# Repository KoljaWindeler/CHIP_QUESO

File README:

please read http://koljawindeler.github.io/CHIP_QUESO

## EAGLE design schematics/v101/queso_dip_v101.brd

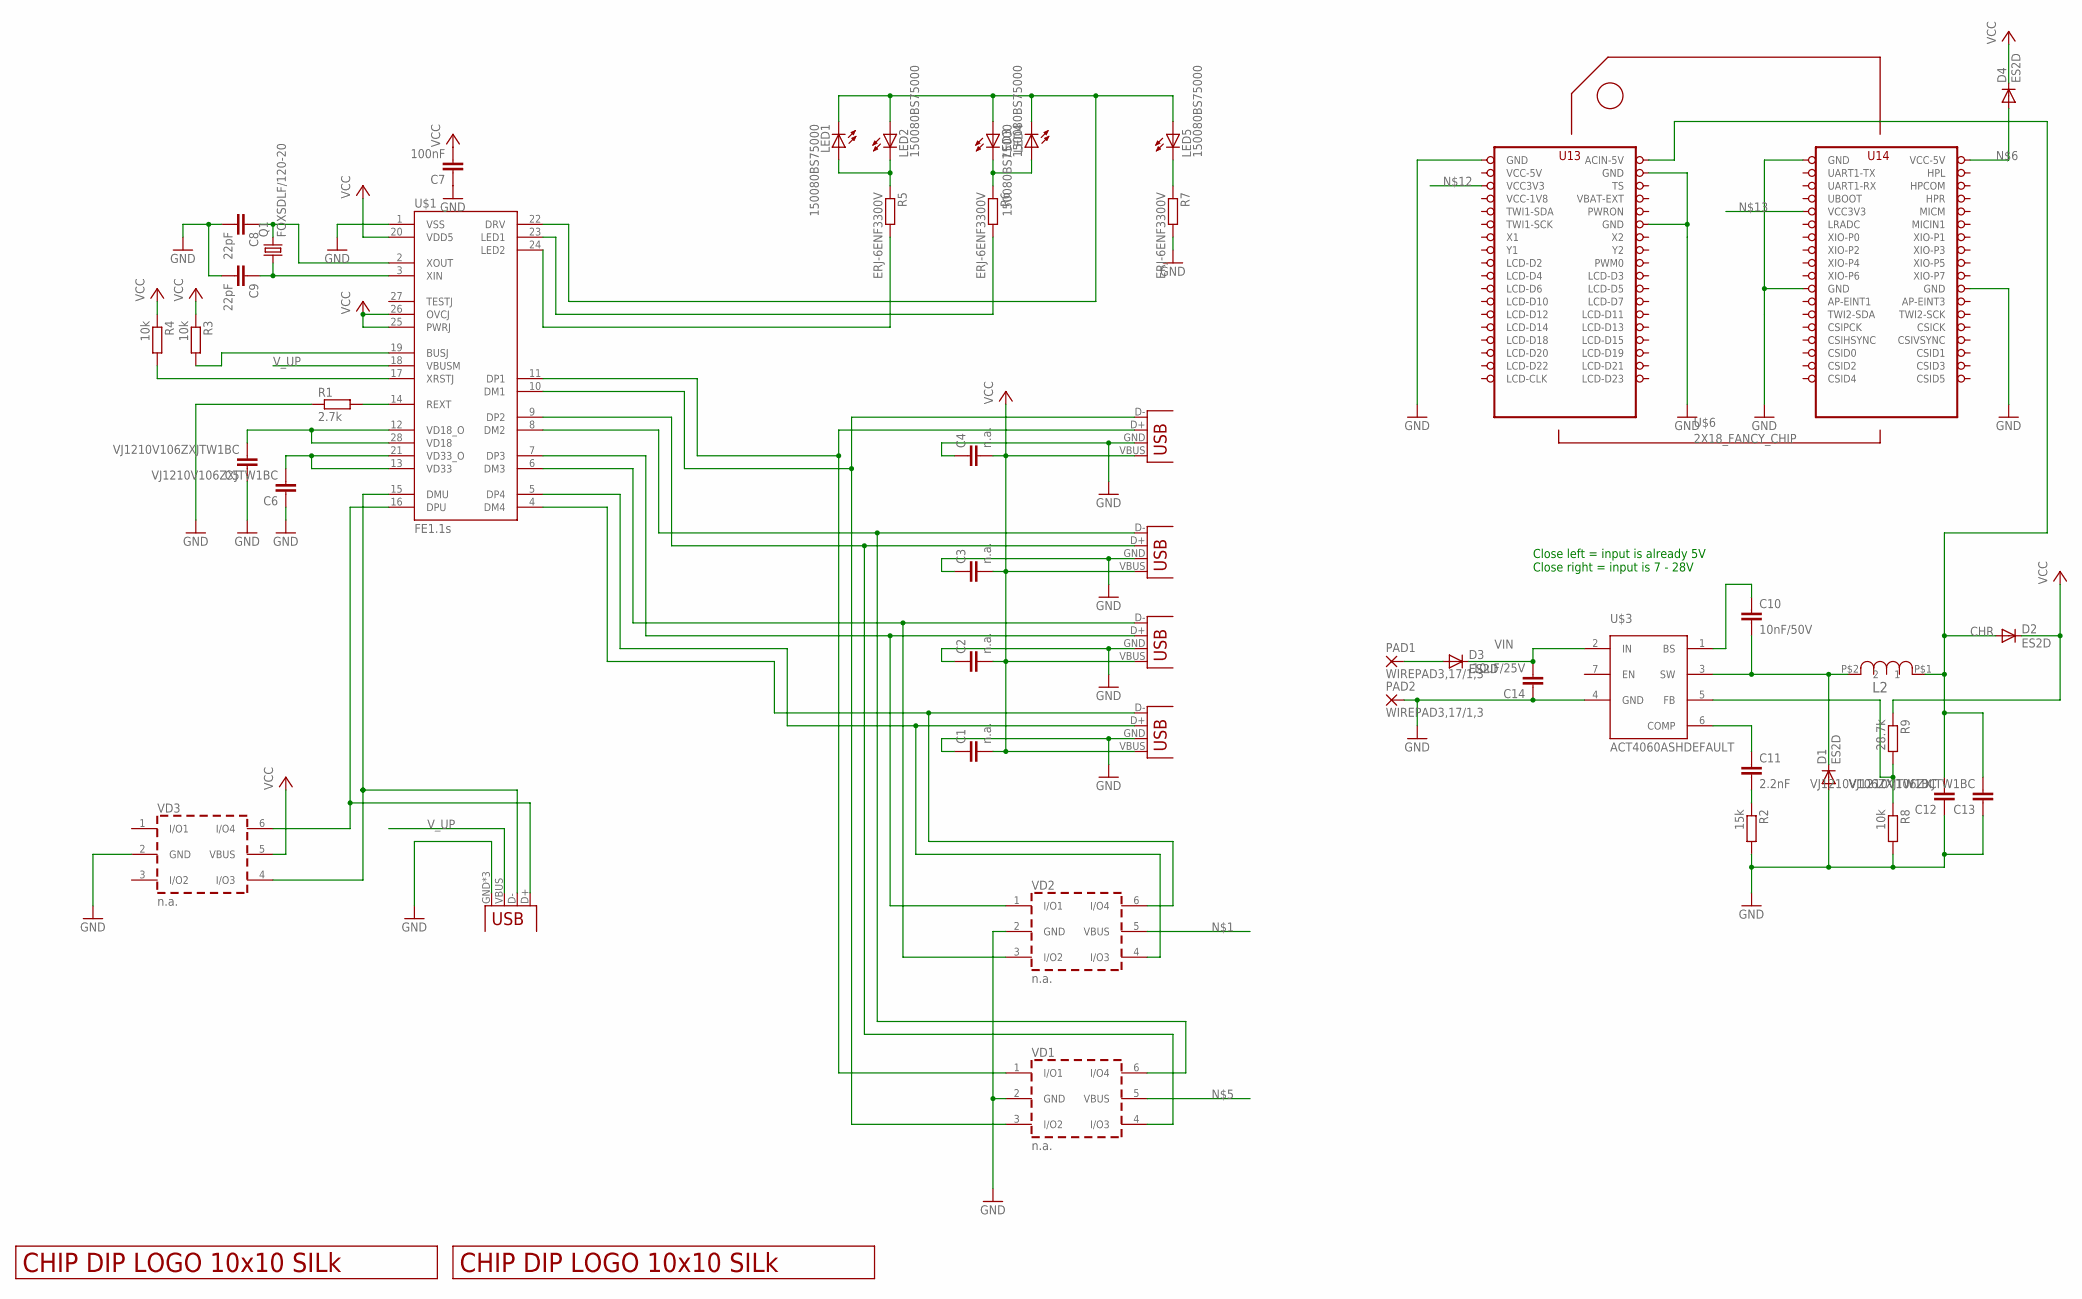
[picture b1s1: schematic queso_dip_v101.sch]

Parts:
C1, C2, C3, C4: n.a.; C1210
C5, C6, C12, C13: VJ1210V106ZXJTW1BC; C1210
C7: 100nF; C0805
C8, C9: 22pF; C0805
C10: 10nF/50V; C0805
C11: 2.2nF; C0805
C14: 10uF/25V; C1210
D1, D2, D3, D4: ES2D; SMB
DATA_USB: USBUSB-MICROB-SMT-DIP; USB-MICROB-SMT-DIP
L2: SRN6045-100M; SRN6045
LED1, LED2, LED3, LED4, LED5: 150080BS75000; CHIP-LED0805
PAD1, PAD2: WIREPAD3,17/1,3; 3,17/1,3
Q1: FOXSDLF/120-20; SM49
R1: 2.7k; R0805
R2: 15k; R0805
R3, R4, R8: 10k; R0805
R5, R6, R7: ERJ-6ENF3300V; R0805
R9: 28.7k; R0805
U$1: FE1.1S; FE1.1S_SSOP-28
U$2, U$4: LOGO_10X10_SILK; LOGO2_10X10_SILK
U$3: ACT4060ASHDEFAULT; SOP-8
U$6: 2X18_FANCY_CHIP; 2X18_FANCY_EDGE_CHIP_TH
VD1, VD2, VD3: n.a.; SOT-23-6L
X1, X2, X3, X4: USB-A-HU

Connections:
CHR: C12.2, C13.2, D2.A, L2.P$1 (1), U$6.36 (ACIN-5V)
DM1: U$1.10 (DM1), VD1.3 (I/O2), X4.D- (D+)
DM2: U$1.8 (DM2), VD1.6 (I/O4), X3.D- (D+)
DM3: U$1.6 (DM3), VD2.3 (I/O2), X2.D- (D+)
DM4: U$1.4 (DM4), VD2.6 (I/O4), X1.D- (D+)
DMU: DATA_USB.D-, U$1.15 (DMU), VD3.4 (I/O3)
DP1: U$1.11 (DP1), VD1.1 (I/O1), X4.D+ (D-)
DP2: U$1.9 (DP2), VD1.4 (I/O3), X3.D+ (D-)
DP3: U$1.7 (DP3), VD2.1 (I/O1), X2.D+ (D-)
DP4: U$1.5 (DP4), VD2.4 (I/O3), X1.D+ (D-)
DPU: DATA_USB.D+, U$1.16 (DPU), VD3.6 (I/O4)
GND: C1.1, C2.1, C3.1, C4.1, C5.1, C6.1, C7.1, C8.2, C9.2, C12.1, C13.1, C14.1, D1.A, DATA_USB.GND, DATA_USB.MT1 (GND), DATA_USB.MT2 (GND), PAD2.1, R1.1, R7.2, R8.2, U$1.1 (VSS), U$3.4 (GND), U$6.26 (GND), U$6.34 (GND), U$6.35 (GND), U$6.51 (GND), U$6.52 (GND), U$6.71 (GND), VD1.2 (GND), VD2.2 (GND), VD3.2 (GND), X1.GND (VBUS), X2.GND (VBUS), X3.GND (VBUS), X4.GND (VBUS)
unnamed: D3.A, PAD1.1
unnamed: D4.A, U$6.72 (VCC-5V)
unnamed: C10.2, D1.C, L2.P$2 (2), U$3.3 (SW)
unnamed: C10.1, U$3.1 (BS)
unnamed: C11.2, R2.1
unnamed: C11.1, U$3.6 (COMP)
unnamed: R8.1, R9.2, U$3.5 (FB)
unnamed: R5.2, U$1.24 (LED2)
unnamed: R6.2, U$1.23 (LED1)
unnamed: C6.2, U$1.13 (VD33), U$1.21 (VD33_O)
unnamed: C5.2, U$1.12 (VD18_O), U$1.28 (VD18)
unnamed: R1.2, U$1.14 (REXT)
unnamed: R4.2, U$1.17 (XRSTJ)
unnamed: R3.2, U$1.19 (BUSJ)
unnamed: C8.1, Q1.2, U$1.2 (XOUT)
unnamed: C9.1, Q1.1, U$1.3 (XIN)
unnamed: LED5.C, R7.1
unnamed: LED3.C, LED4.A, R6.1
unnamed: LED1.A, LED2.C, R5.1
unnamed: LED1.C, LED2.A, LED3.A, LED4.C, LED5.A, U$1.22 (DRV)
VCC: C1.2, C2.2, C3.2, C4.2, C7.2, D2.C, D4.C, R3.1, R4.1, R9.1, U$1.20 (VDD5), U$1.25 (PWRJ), U$1.26 (OVCJ), VD3.5 (VBUS), X1.VBUS (GND), X2.VBUS (GND), X3.VBUS (GND), X4.VBUS (GND)
VCC-1V8: U$6.29 (VCC-1V8)
VCC-5V: U$6.33 (VCC-5V)
VIN: C14.2, D3.C, U$3.2 (IN)
V_UP: DATA_USB.VBUS, U$1.18 (VBUSM)

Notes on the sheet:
Close left = input is already 5V Close right = input is 7 - 28V

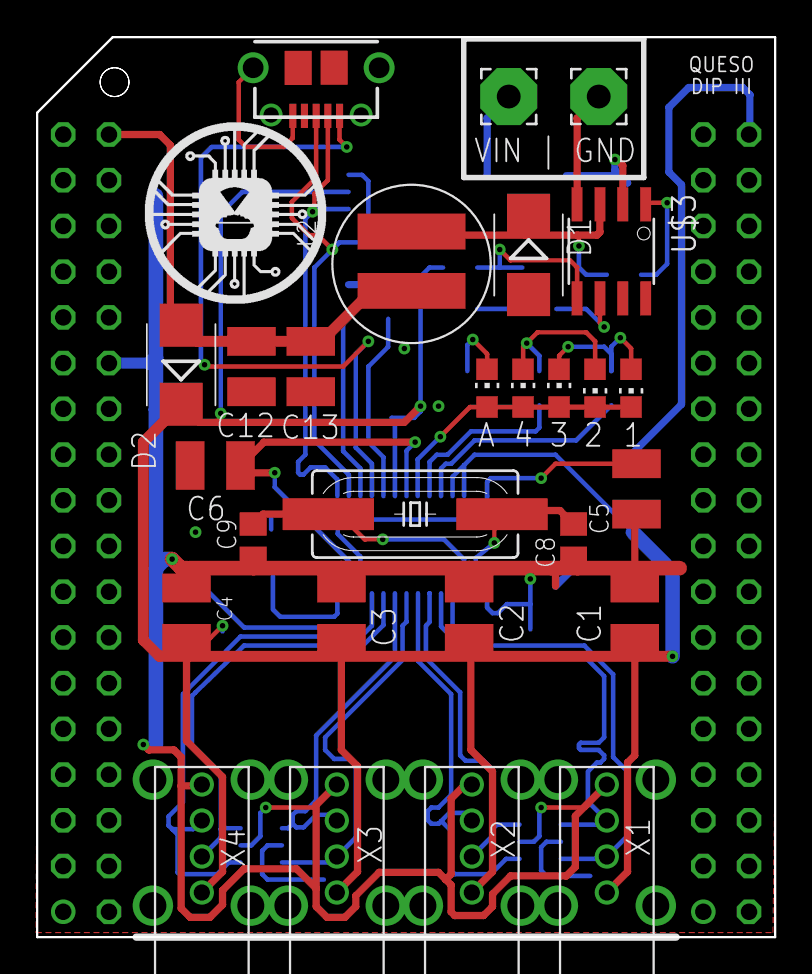
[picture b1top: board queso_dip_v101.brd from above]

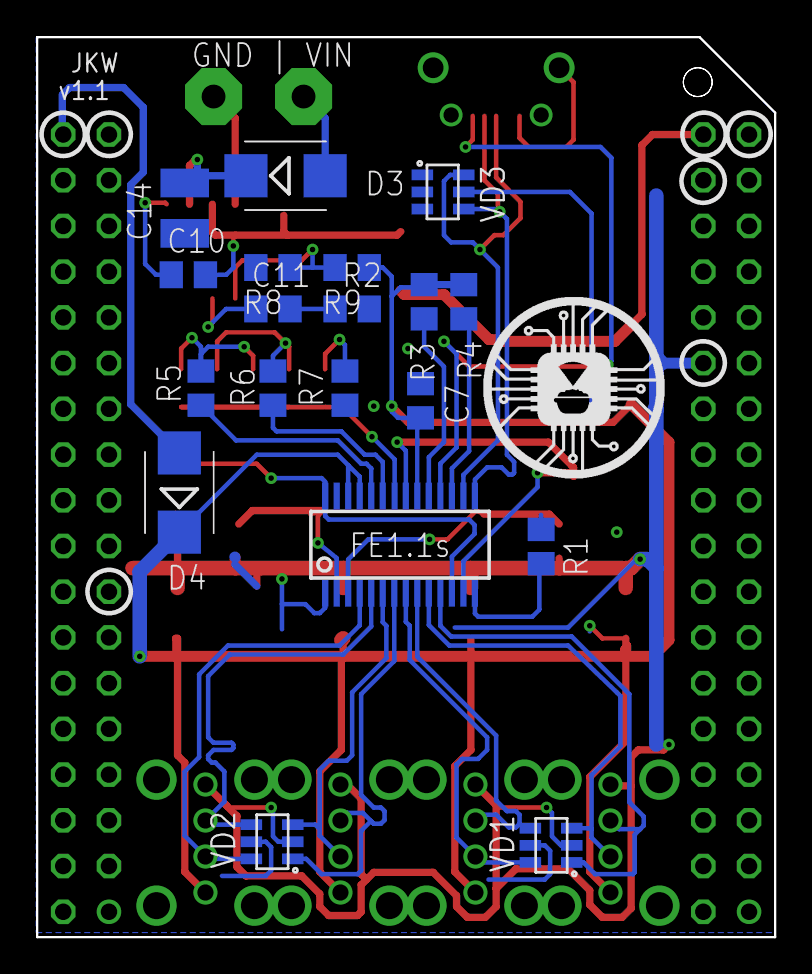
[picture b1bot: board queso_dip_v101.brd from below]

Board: 2 copper layers, 41.0 x 50.0 mm, 49 parts (20 on the bottom side), 35 nets.

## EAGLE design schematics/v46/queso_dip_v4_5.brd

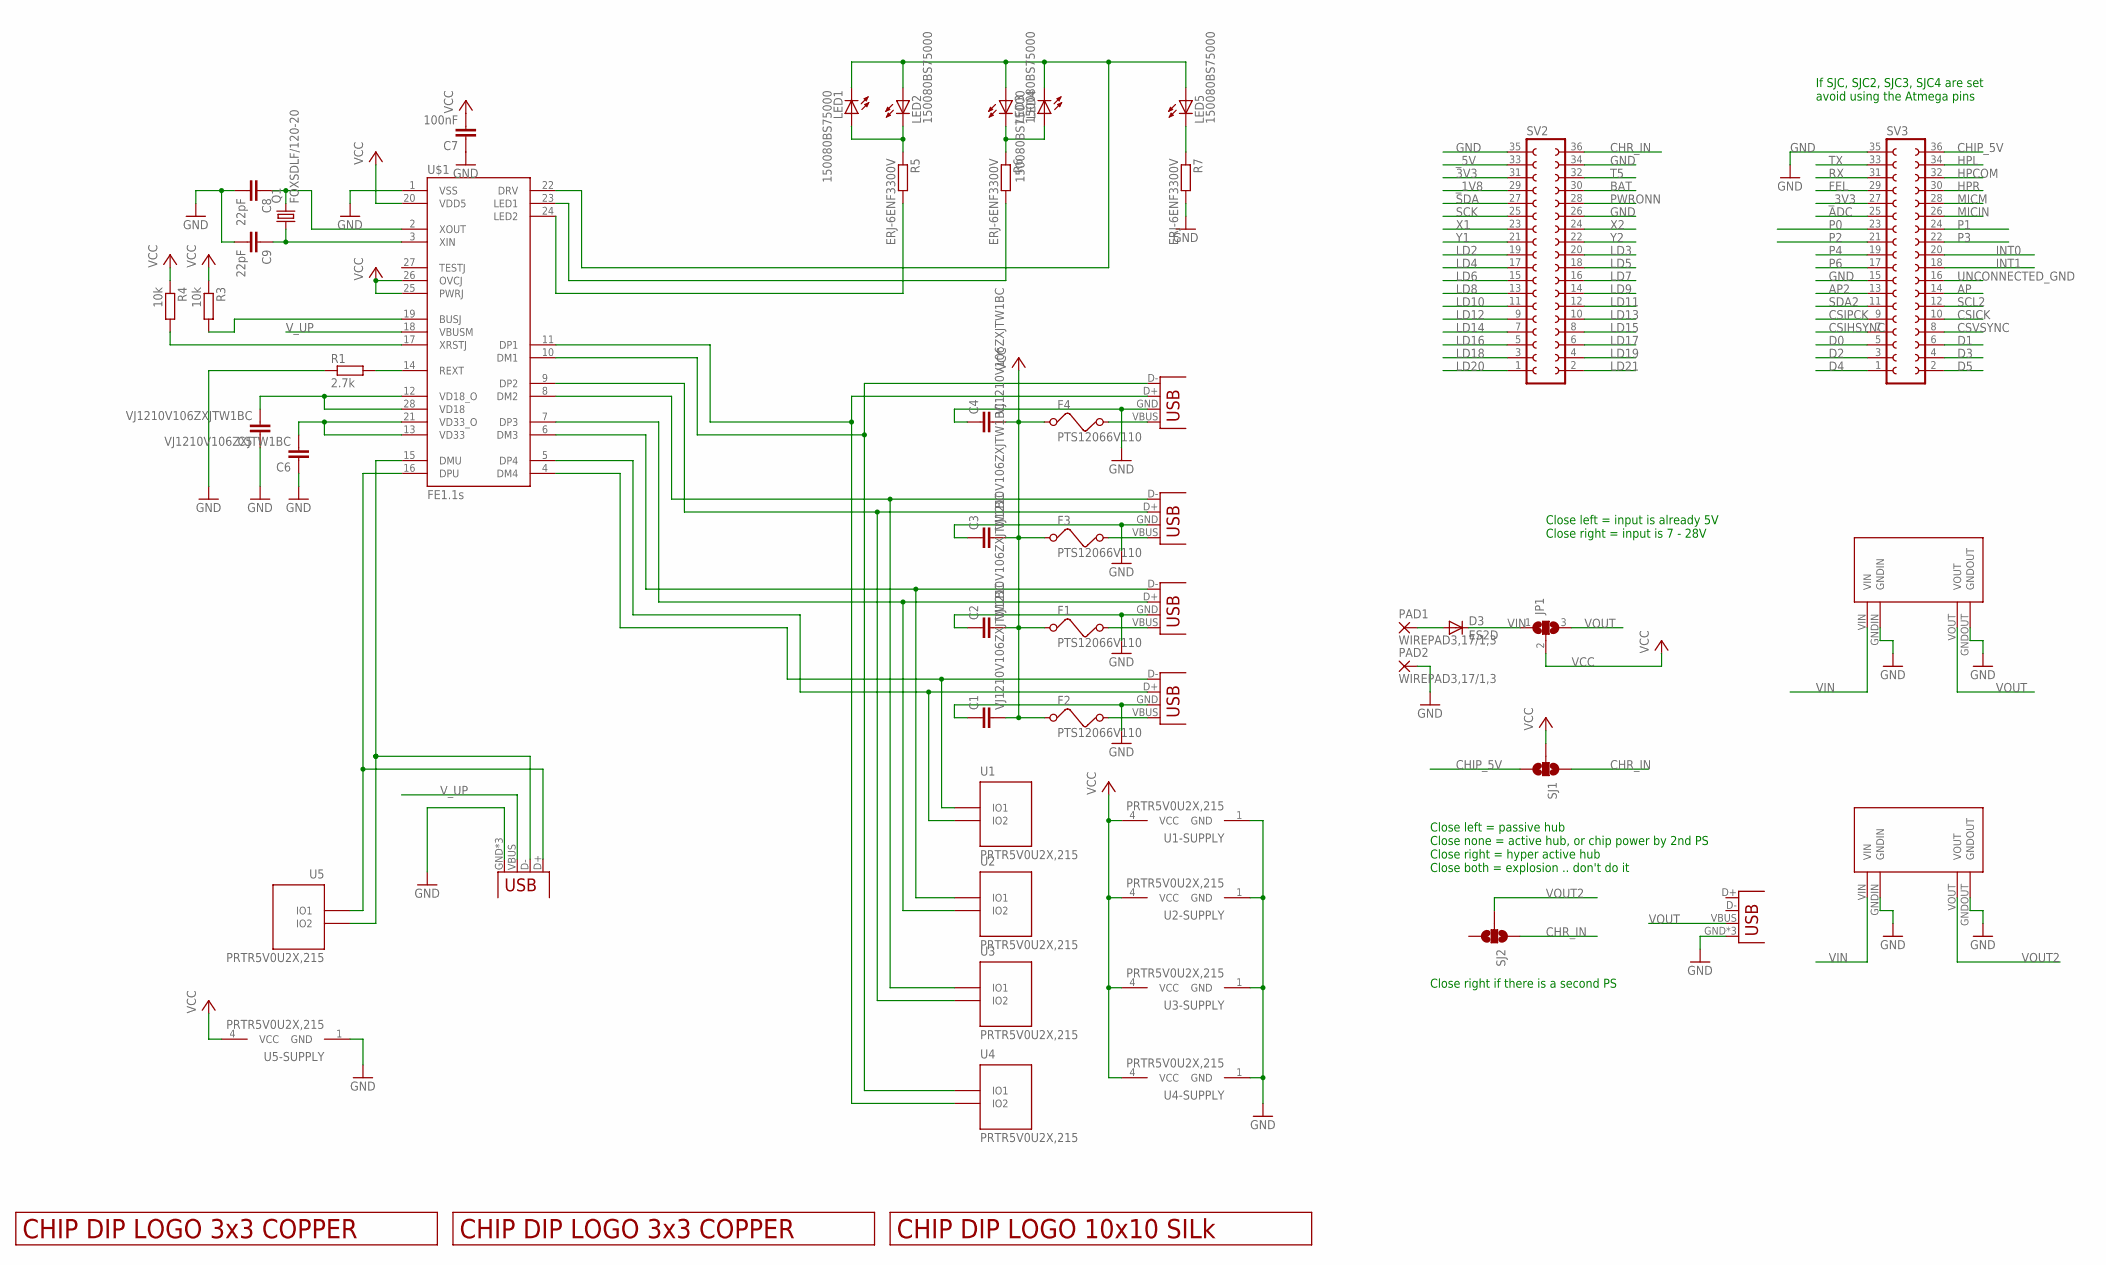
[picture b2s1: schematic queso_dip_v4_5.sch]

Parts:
C1, C2, C3, C4, C5, C6: VJ1210V106ZXJTW1BC; C1210
C7: 100nF; C0805
C8, C9: 22pF; C0805
D3: ES2D; SMB
F1, F2, F3, F4: PTS12066V110; 1210
JP1: SJ2W; SJ_2
LED1, LED2, LED3, LED4, LED5: 150080BS75000; CHIP-LED0805
PAD1, PAD2: WIREPAD3,17/1,3; 3,17/1,3
Q1: FOXSDLF/120-20; SM49
R1: 2.7k; R0805
R3, R4: 10k; R0805
R5, R6, R7: ERJ-6ENF3300V; R0805
SJ1, SJ2: SOLDERJUMPER_2WAYT; SJ_2
SV2, SV3: FE18-2
U1, U2, U3, U4, U5: PRTR5V0U2X,215; SOT-143B
U$1: FE1.1S; FE1.1S_SSOP-28
U$2, U$4: LOGO_3X3_COPPER
U$3, U$9: MP1584EN
U$5: LOGO_10X10_SILK
USB, USB1: USBUSB-MICROB-SMT-DIP; USB-MICROB-SMT-DIP
X1, X2, X3, X4: USB-A-HU

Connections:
3V3: SV2.31
ADC: SV3.25
AP: SV3.14
AP2: SV3.13
BAT: SV2.30
CHIP_5V: SJ1.3, SV3.36
CHR_IN: SJ1.1, SJ2.1, SV2.36
CSICK: SV3.10
CSIHSYNC: SV3.7
CSIPCK: SV3.9
CSVSYNC: SV3.8
D0: SV3.5
D1: SV3.6
D2: SV3.3
D3: SV3.4
D4: SV3.1
D5: SV3.2
DM1: U4.2 (IO1), U$1.10 (DM1), X4.D- (D+)
DM2: U3.2 (IO1), U$1.8 (DM2), X3.D- (D+)
DM3: U2.2 (IO1), U$1.6 (DM3), X2.D- (D+)
DM4: U1.2 (IO1), U$1.4 (DM4), X1.D- (D+)
DMU: U5.3 (IO2), U$1.15 (DMU), USB.D-
DP1: U4.3 (IO2), U$1.11 (DP1), X4.D+ (D-)
DP2: U3.3 (IO2), U$1.9 (DP2), X3.D+ (D-)
DP3: U2.3 (IO2), U$1.7 (DP3), X2.D+ (D-)
DP4: U1.3 (IO2), U$1.5 (DP4), X1.D+ (D-)
DPU: U5.2 (IO1), U$1.16 (DPU), USB.D+
FEL: SV3.29
GND: C1.1, C2.1, C3.1, C4.1, C5.1, C6.1, C7.1, C8.2, C9.2, PAD2.1, R1.1, R7.2, SV2.26, SV2.34, SV2.35, SV3.15, SV3.35, U1.1 (GND), U2.1 (GND), U3.1 (GND), U4.1 (GND), U5.1 (GND), U$1.1 (VSS), U$3.GNDIN, U$3.GNDOUT, U$9.GNDIN, U$9.GNDOUT, USB.GND, USB.MT1 (GND), USB.MT2 (GND), USB1.GND, USB1.MT1 (GND), USB1.MT2 (GND), X1.GND (VBUS), X2.GND (VBUS), X3.GND (VBUS), X4.GND (VBUS)
HPCOM: SV3.32
HPL: SV3.34
HPR: SV3.30
INT0: SV3.20
INT1: SV3.18
LD2: SV2.19
LD3: SV2.20
LD4: SV2.17
LD5: SV2.18
LD6: SV2.15
LD7: SV2.16
LD8: SV2.13
LD9: SV2.14
LD10: SV2.11
LD11: SV2.12
LD12: SV2.9
LD13: SV2.10
LD14: SV2.7
LD15: SV2.8
LD16: SV2.5
LD17: SV2.6
LD18: SV2.3
LD19: SV2.4
LD20: SV2.1
LD21: SV2.2
MICIN: SV3.26
MICM: SV3.28
unnamed: F2.2, X1.VBUS (GND)
unnamed: D3.A, PAD1.1
unnamed: F4.2, X4.VBUS (GND)
unnamed: F1.2, X2.VBUS (GND)
unnamed: F3.2, X3.VBUS (GND)
unnamed: R5.2, U$1.24 (LED2)
unnamed: R6.2, U$1.23 (LED1)
unnamed: C6.2, U$1.13 (VD33), U$1.21 (VD33_O)
unnamed: C5.2, U$1.12 (VD18_O), U$1.28 (VD18)
unnamed: R1.2, U$1.14 (REXT)
unnamed: R4.2, U$1.17 (XRSTJ)
unnamed: R3.2, U$1.19 (BUSJ)
unnamed: C8.1, Q1.2, U$1.2 (XOUT)
unnamed: C9.1, Q1.1, U$1.3 (XIN)
unnamed: LED5.C, R7.1
unnamed: LED3.C, LED4.A, R6.1
unnamed: LED1.A, LED2.C, R5.1
unnamed: LED1.C, LED2.A, LED3.A, LED4.C, LED5.A, U$1.22 (DRV)
P0: SV3.23
P1: SV3.24
P2: SV3.21
P3: SV3.22
P4: SV3.19
P6: SV3.17
PWRONN: SV2.28
RX: SV3.31
SCK: SV2.25
SCL2: SV3.12
SDA: SV2.27
SDA2: SV3.11
T5: SV2.32
TX: SV3.33
UNCONNECTED_GND: SV3.16
VCC: C1.2, C2.2, C3.2, C4.2, C7.2, F1.1, F2.1, F3.1, F4.1, JP1.2, R3.1, R4.1, SJ1.2, U1.4 (VCC), U2.4 (VCC), U3.4 (VCC), U4.4 (VCC), U5.4 (VCC), U$1.20 (VDD5), U$1.25 (PWRJ), U$1.26 (OVCJ)
VIN: D3.C, JP1.1, U$3.VIN, U$9.VIN
VOUT: JP1.3, U$9.VOUT, USB1.VBUS
VOUT2: SJ2.2, U$3.VOUT
V_UP: U$1.18 (VBUSM), USB.VBUS
X1: SV2.23
X2: SV2.24
Y1: SV2.21
Y2: SV2.22
_1V8: SV2.29
_3V3: SV3.27
_5V: SV2.33

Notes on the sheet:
If SJC, SJC2, SJC3, SJC4 are set avoid using the Atmega pins
Close left = passive hub Close none = active hub, or chip power by 2nd PS Close right = hyper active hub Close both = explosion .. don't do it
Close left = input is already 5V Close right = input is 7 - 28V
Close right if there is a second PS

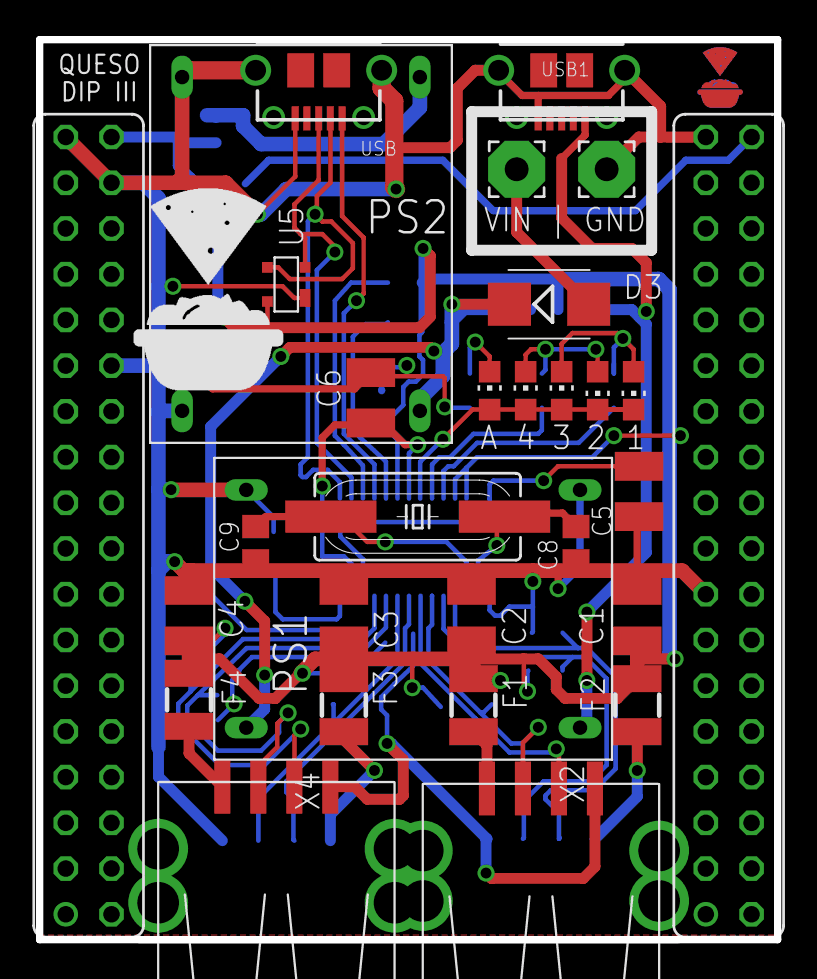
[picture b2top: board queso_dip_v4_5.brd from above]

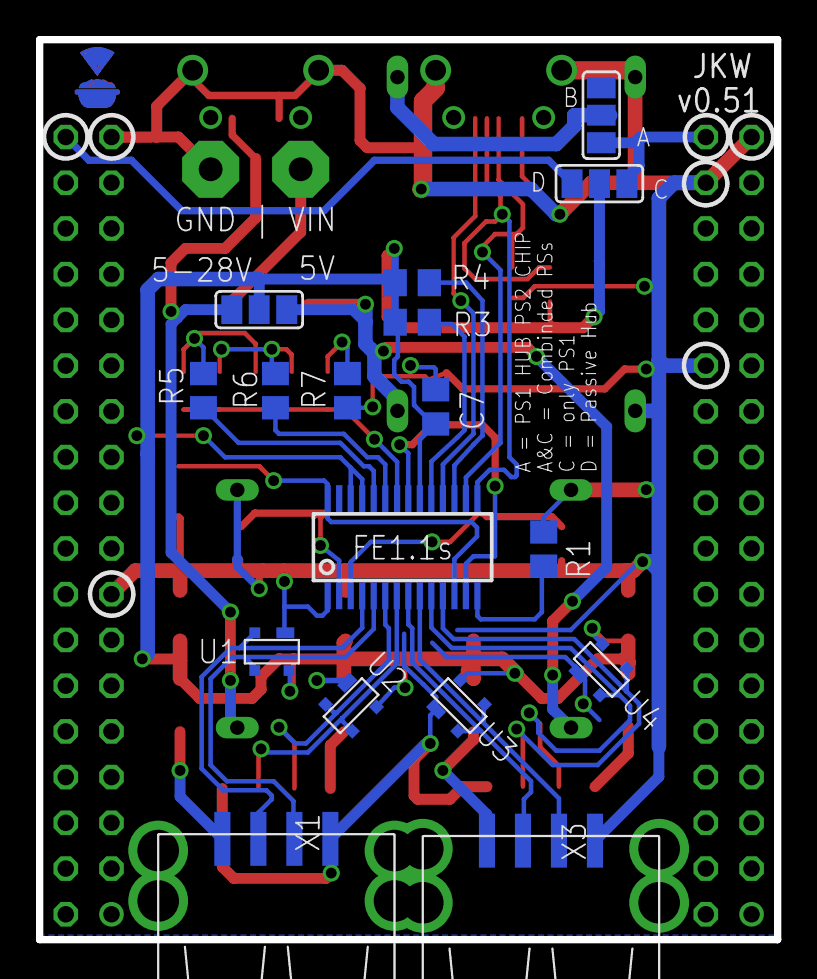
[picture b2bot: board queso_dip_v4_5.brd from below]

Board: 2 copper layers, 41.0 x 50.0 mm, 50 parts (18 on the bottom side), 36 nets.

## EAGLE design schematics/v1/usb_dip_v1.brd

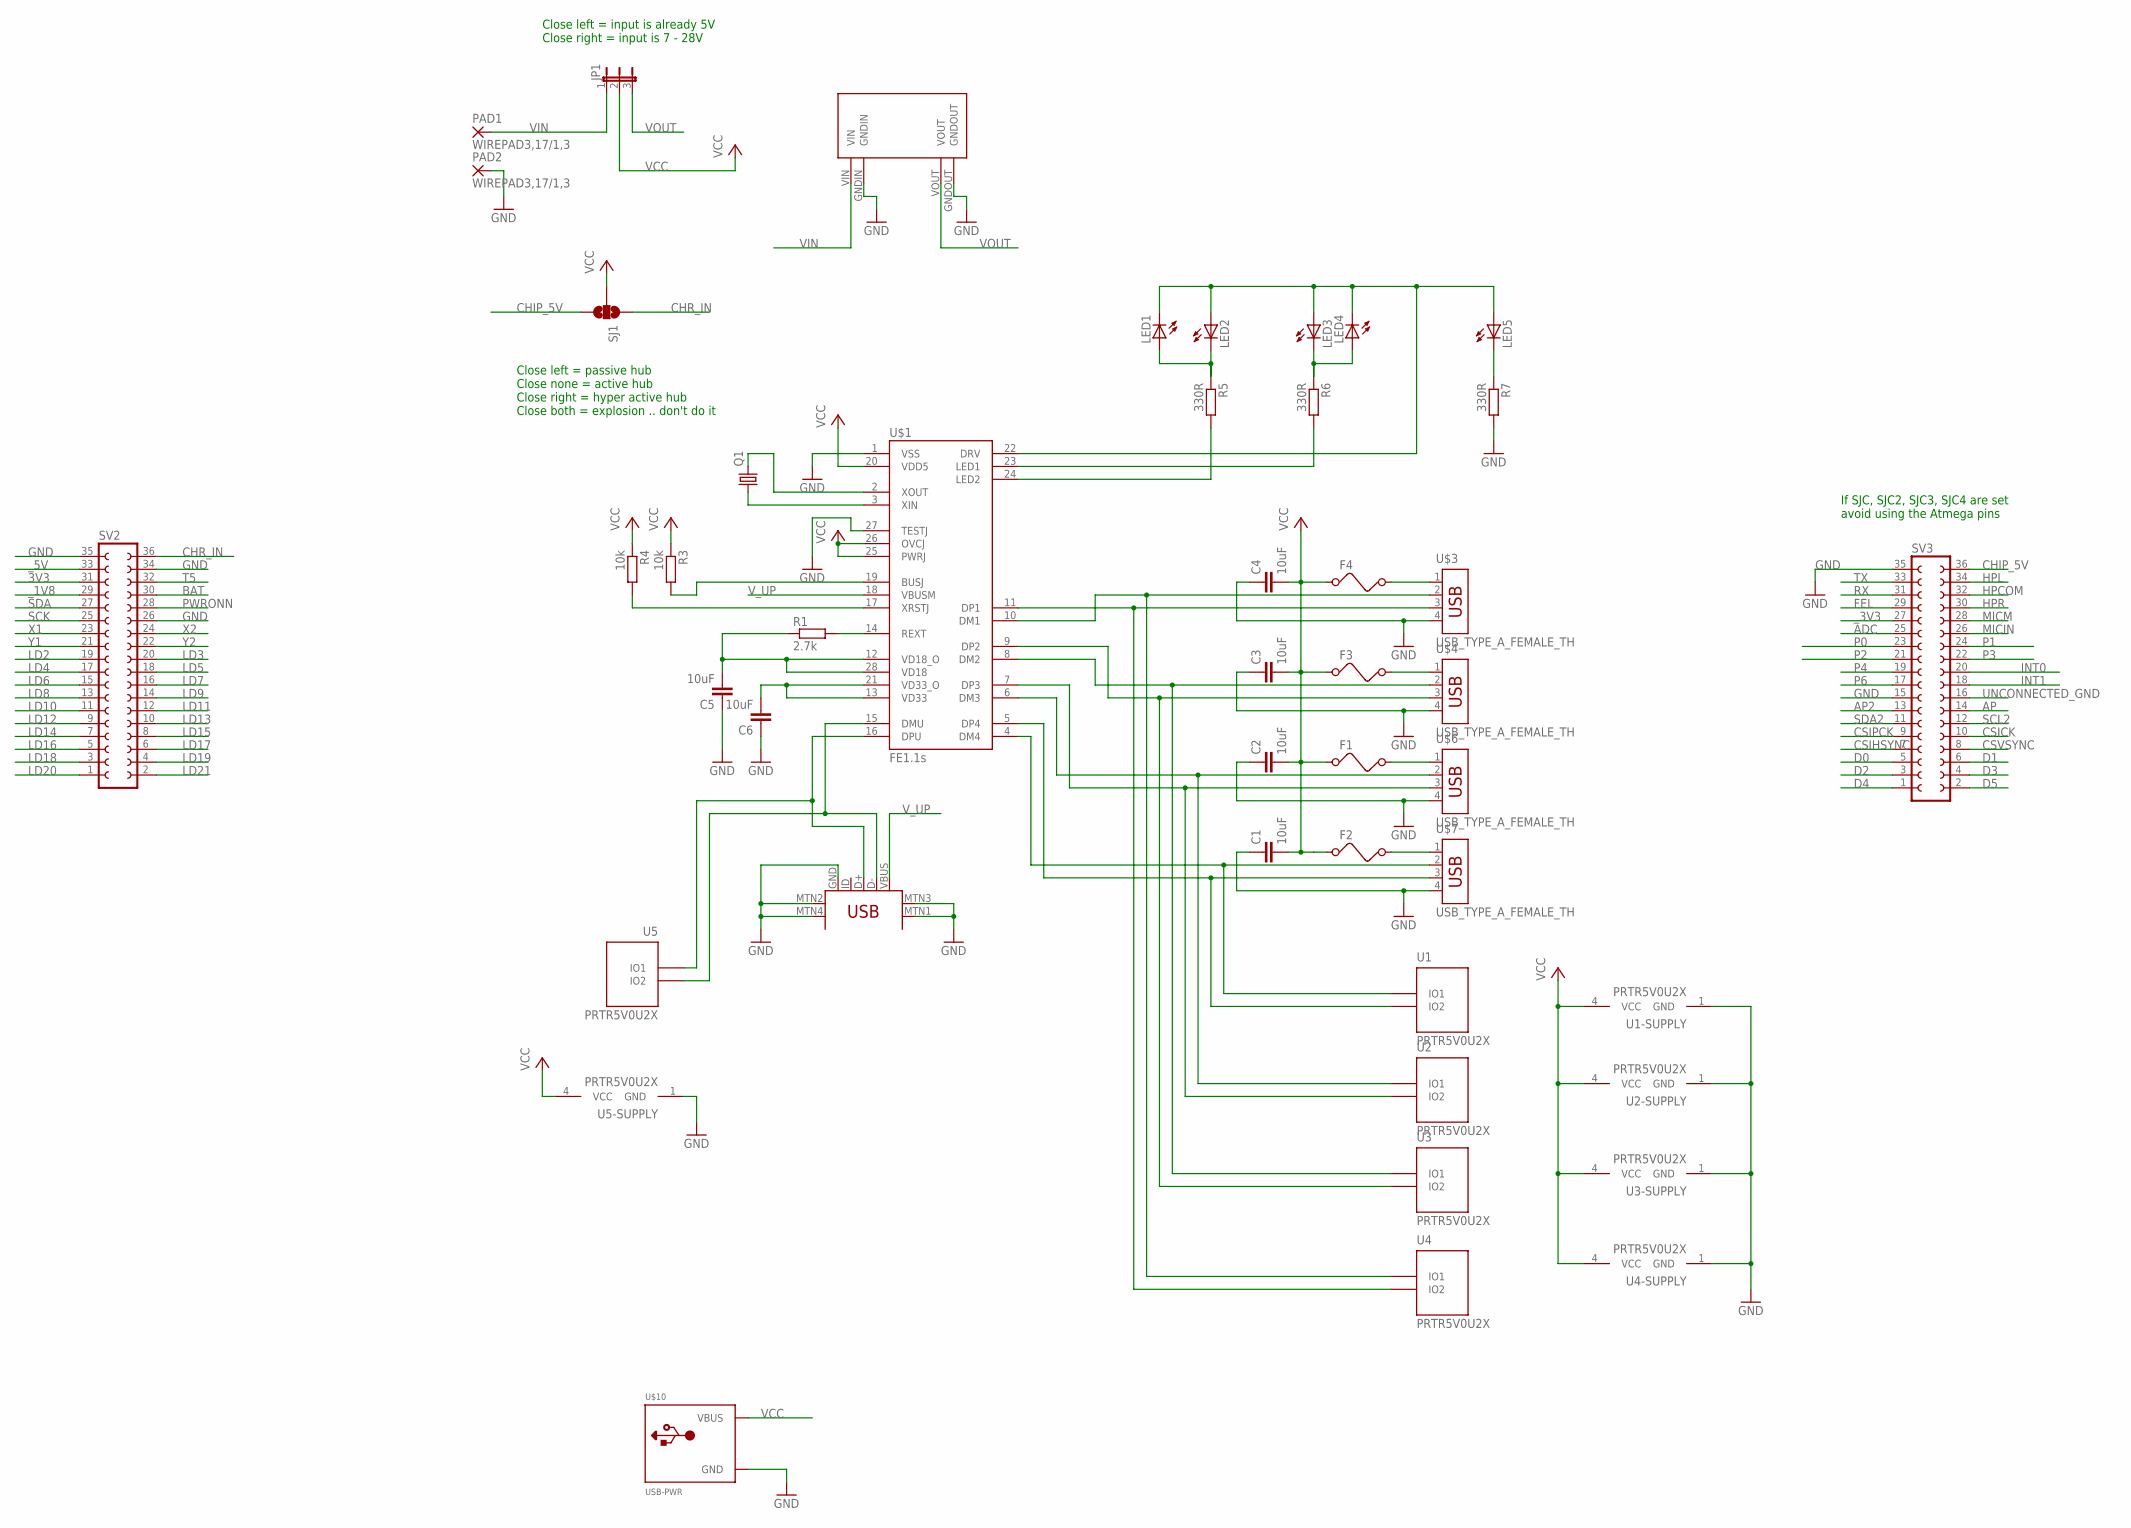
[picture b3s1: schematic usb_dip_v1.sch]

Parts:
C1, C2, C3, C4, C5, C6: 10uF; C1210
F1, F2, F3, F4: FUSED; 1210
JP1: JP2E; JP2
LED1, LED2, LED3, LED4, LED5: LEDCHIP-LED0805; CHIP-LED0805
PAD1, PAD2: WIREPAD3,17/1,3; 3,17/1,3
Q1: CRYSTALSM49; SM49
R1: 2.7k; R0805
R3, R4: 10k; R0805
R5, R6, R7: 330R; R0805
SJ1: SOLDERJUMPER_2WAYT; SJ_2
SV2, SV3: FE18-2
U1, U2, U3, U4, U5: PRTR5V0U2X; SOT-143B
U$1: FE1.1S; FE1.1S_SSOP-28
U$3, U$4, U$6, U$7: USB_TYPE_A_FEMALE_TH
U$8: USB-MINIB-5PIN; USB-MINIB
U$9: MP1584EN
U$10: USB-PWR; USB-MINIB-THM-MOLEX-PWRONLY

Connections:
3V3: SV2.31
ADC: SV3.25
AP: SV3.14
AP2: SV3.13
BAT: SV2.30
CHIP_5V: SJ1.3, SV3.36
CHR_IN: SJ1.1, SV2.36
CSICK: SV3.10
CSIHSYNC: SV3.7
CSIPCK: SV3.9
CSVSYNC: SV3.8
D0: SV3.5
D1: SV3.6
D2: SV3.3
D3: SV3.4
D4: SV3.1
D5: SV3.2
DM1: U4.2 (IO1), U$1.10 (DM1), U$3.2
DM2: U3.2 (IO1), U$1.8 (DM2), U$4.2
DM3: U2.2 (IO1), U$1.6 (DM3), U$6.2
DM4: U1.2 (IO1), U$1.4 (DM4), U$7.2
DMU: U5.3 (IO2), U$1.15 (DMU), U$8.D-
DP1: U4.3 (IO2), U$1.11 (DP1), U$3.3
DP2: U3.3 (IO2), U$1.9 (DP2), U$4.3
DP3: U2.3 (IO2), U$1.7 (DP3), U$6.3
DP4: U1.3 (IO2), U$1.5 (DP4), U$7.3
DPU: U5.2 (IO1), U$1.16 (DPU), U$8.D+
FEL: SV3.29
GND: C1.1, C2.1, C3.1, C4.1, C5.1, C6.1, PAD2.1, R7.2, SV2.26, SV2.34, SV2.35, SV3.15, SV3.35, U1.1 (GND), U2.1 (GND), U3.1 (GND), U4.1 (GND), U5.1 (GND), U$1.1 (VSS), U$1.27 (TESTJ), U$3.4, U$4.4, U$6.4, U$7.4, U$8.GND, U$8.MTN1 (MTN2), U$8.MTN2 (MTN3), U$8.MTN3 (MTN1), U$8.MTN4, U$9.GNDIN, U$9.GNDOUT, U$10.GND
HPCOM: SV3.32
HPL: SV3.34
HPR: SV3.30
INT0: SV3.20
INT1: SV3.18
LD2: SV2.19
LD3: SV2.20
LD4: SV2.17
LD5: SV2.18
LD6: SV2.15
LD7: SV2.16
LD8: SV2.13
LD9: SV2.14
LD10: SV2.11
LD11: SV2.12
LD12: SV2.9
LD13: SV2.10
LD14: SV2.7
LD15: SV2.8
LD16: SV2.5
LD17: SV2.6
LD18: SV2.3
LD19: SV2.4
LD20: SV2.1
LD21: SV2.2
MICIN: SV3.26
MICM: SV3.28
unnamed: F2.2, U$7.1
unnamed: F1.2, U$6.1
unnamed: F3.2, U$4.1
unnamed: F4.2, U$3.1
unnamed: R5.2, U$1.24 (LED2)
unnamed: R6.2, U$1.23 (LED1)
unnamed: C6.2, U$1.13 (VD33), U$1.21 (VD33_O)
unnamed: C5.2, R1.1, U$1.12 (VD18_O), U$1.28 (VD18)
unnamed: R1.2, U$1.14 (REXT)
unnamed: R4.2, U$1.17 (XRSTJ)
unnamed: R3.2, U$1.19 (BUSJ)
unnamed: Q1.2, U$1.2 (XOUT)
unnamed: Q1.1, U$1.3 (XIN)
unnamed: LED5.C, R7.1
unnamed: LED3.C, LED4.A, R6.1
unnamed: LED1.A, LED2.C, R5.1
unnamed: LED1.C, LED2.A, LED3.A, LED4.C, LED5.A, U$1.22 (DRV)
P0: SV3.23
P1: SV3.24
P2: SV3.21
P3: SV3.22
P4: SV3.19
P6: SV3.17
PWRONN: SV2.28
RX: SV3.31
SCK: SV2.25
SCL2: SV3.12
SDA: SV2.27
SDA2: SV3.11
T5: SV2.32
TX: SV3.33
UNCONNECTED_GND: SV3.16
VCC: C1.2, C2.2, C3.2, C4.2, F1.1, F2.1, F3.1, F4.1, JP1.2, R3.1, R4.1, SJ1.2, U1.4 (VCC), U2.4 (VCC), U3.4 (VCC), U4.4 (VCC), U5.4 (VCC), U$1.20 (VDD5), U$1.25 (PWRJ), U$1.26 (OVCJ), U$10.VBUS
VIN: JP1.1, PAD1.1, U$9.VIN
VOUT: JP1.3, U$9.VOUT
V_UP: U$1.18 (VBUSM), U$8.VBUS
X1: SV2.23
X2: SV2.24
Y1: SV2.21
Y2: SV2.22
_1V8: SV2.29
_3V3: SV3.27
_5V: SV2.33

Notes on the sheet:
If SJC, SJC2, SJC3, SJC4 are set avoid using the Atmega pins
Close left = passive hub Close none = active hub Close right = hyper active hub Close both = explosion .. don't do it
Close left = input is already 5V Close right = input is 7 - 28V

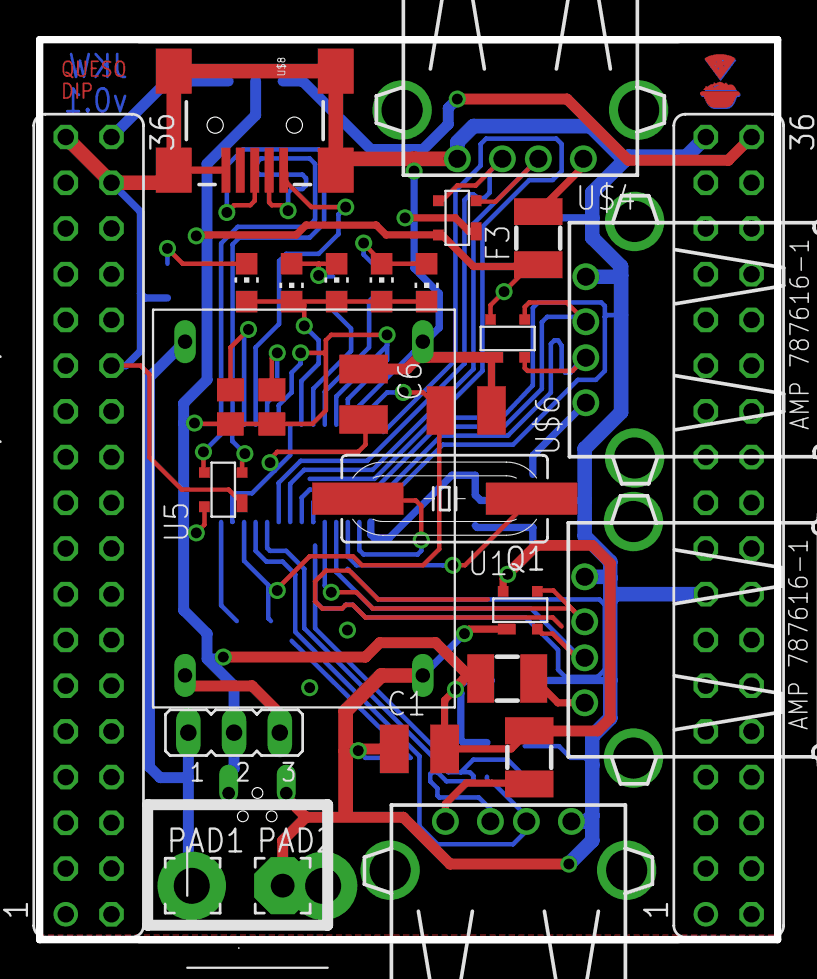
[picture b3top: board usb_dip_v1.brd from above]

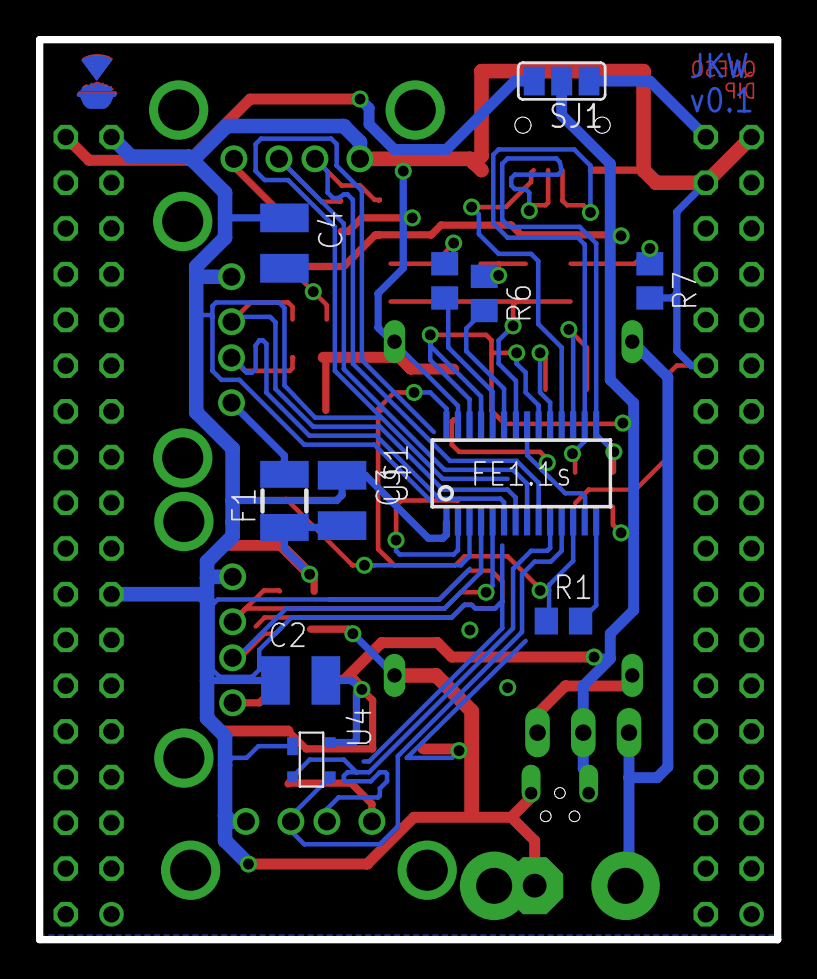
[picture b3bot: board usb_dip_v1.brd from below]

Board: 2 copper layers, 41.0 x 50.0 mm, 43 parts (12 on the bottom side), 34 nets.

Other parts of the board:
U$2, U$5: LOGO

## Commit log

2016-03-01 :neckbeard: Added .gitattributes & .gitignore files
2016-03-01 move schematics to subdir and added doc
2016-03-02 osh order
2016-03-02 Ordered Board v1 at OSH and seeed, renamed dev version
2016-03-07 added new version
2016-03-07 routing for version3
2016-03-09 improved silkscreen
2016-03-09 added gerber + bom
2016-03-10 renamed screen for windows
2016-03-10 cleaned schematic, rearranged leds (again)
2016-03-10 upated ignore file for eagle temp files
2016-03-12 added Elecrow files
2016-03-12 v4, final version for vertical jacks
2016-03-12 dual double jacks
2016-03-12 added order notes to all boards
2016-03-12 commit temp files
2016-03-15 fixed micro usb
2016-03-15 removed temp
2016-03-15 add spark lib with corrected USB footprint
2016-03-15 version with stacked USB
2016-03-15 clean up
2016-03-15 added logo
2016-03-15 logo
2016-03-15 added silk logo
2016-03-15 clean
2016-03-16 new logo
2016-03-16 remove temp file
2016-03-17 ordered v4 with correct vss
2016-03-17 added photos, disconnect TESTPIN
2016-03-27 updated v4.4
2016-03-27 Create gh-pages branch via GitHub
2016-03-27 add readme
2016-04-03 added version 0.45, crystal load caps, polarity protection diode
2016-04-03 fixed rotated label
2016-04-07 init docu
2016-04-11 adapter to save queso
2016-04-28 sch + adapter
2016-04-29 added usb powered version
2016-05-03 added flat usb version
2016-05-03 moved v45 to ordered
2016-05-06 added labels for voltage check, moved version label, cut corner off
2016-06-20 fixed DRC
2016-06-20 legacy adapter
2016-06-20 added edge
2016-07-15 replaced ESD diode and added quote
2016-07-19 ordered v49
2016-07-19 added reduced cost version,
2016-07-20 added assembly drawing
2016-07-20 moved quotations to dedicated folder
2016-07-20 added assembly help
2016-07-20 added gerber files, modified vias to miniumum drill and added aliexpress link to quotation
2016-07-21 moved libs, dru, cam to common
2016-08-29 moved gerber to subfolder
2016-10-17 updated quatation, v49_ordered design
2016-12-06 added onboard power supply
2016-12-06 removed v100
2016-12-20 added dual power

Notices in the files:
parts and their libraries:
SparkFun-Connectors: Licensing: Creative Commons ShareAlike 4.0 International - https://creativecommons.org/licenses/by-sa/4.0
m-pad-2.1: License : GNU General Public License version 2 (see bottom)
